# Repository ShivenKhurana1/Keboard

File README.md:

# Keboard

A custom 60% mechanical keyboard featuring an OLED display and rotary encoder for enhanced functionality. coded using [onshape](https://cad.onshape.com/documents/cca7080cfaf346b1d03e6a45/w/840138e854193d740b07961a/e/62251870f6a2fd42355be13b)

## Features

- **60% Layout**: Compact 60-key layout without function row, navigation cluster, or numpad
- **OLED Display**: 0.91" I2C OLED for displaying status, layers, or custom animations
- **Rotary Encoder**: EC11 rotary encoder for volume control, scrolling, or custom functions
- **Hot-Swap Sockets**: Kailh hot-swap sockets for easy switch swapping without soldering
- **RP2040 Controller**: Powered by Raspberry Pi Pico for excellent performance and QMK compatibility

## Gallery

### CAD Design

### Schematics

### PCB Design

## Bill of Materials

|Item                          |Qty  |Link                                                                                                                                                                                                                                                                                                                                                                                                                                                                                                                                                                                                                                                                                                                                                                                                                                                                                                                                    |Price |Running total|
|------------------------------|-----|----------------------------------------------------------------------------------------------------------------------------------------------------------------------------------------------------------------------------------------------------------------------------------------------------------------------------------------------------------------------------------------------------------------------------------------------------------------------------------------------------------------------------------------------------------------------------------------------------------------------------------------------------------------------------------------------------------------------------------------------------------------------------------------------------------------------------------------------------------------------------------------------------------------------------------------|------|-------------|
|Keycaps                       |1 set|[Aliexpress](https://www.aliexpress.us/item/3256809438061445.html?gatewayAdapt=glo2usa4itemAdapt)                                                                                                                                                                                                                                                                                                                                                                                                                                                                                                                                                                                                                                                                                                                                                                                                                                       |13$   |13$          |
|Switches                      |90pc |[Akko V3 Creamy Purple Pro Switch](https://en.akkogear.com/product/akko-v3-creamy-purple-pro-switch/?attribute_quantity=45+pcs&wmc-currency=USD&srsltid=AfmBOoqiLOo9XCgXVcATHmXp4RFQoOtLwqSfavUuphAmf-L9G720cljCm9w)                                                                                                                                                                                                                                                                                                                                                                                                                                                                                                                                                                                                                                                                                                                    |$30.25|43$          |
|OLED                          |1    |[0.91 Inch OLED Display](https://www.aliexpress.us/item/3256808609571956.html?spm=a2g0o.productlist.main.3.48151769KArKuF&algo_pvid=ce0853be-5666-4ee8-8396-2d05b5408b98&algo_exp_id=ce0853be-5666-4ee8-8396-2d05b5408b98-2&pdp_ext_f=%7B%22order%22%3A%2214%22%2C%22eval%22%3A%221%22%2C%22fromPage%22%3A%22search%22%7D&pdp_npi=6%40dis%21USD%215.55%212.49%21%21%2138.01%2117.03%21%402103129017744729562121748e4280%2112000046697912867%21sea%21US%217473440140%21ABX%211%210%21n_tag%3A-29910%3Bd%3A6e694963%3Bm03_new_user%3A-29895%3BpisId%3A5000000200860533&curPageLogUid=osvBYXtlXRIq&utparam-url=scene%3Asearch%7Cquery_from%3A%7Cx_object_id%3A1005008795886708%7C_p_origin_prod%3A)                                                                                                                                                                                                                                        |$5.55 |49$          |
|Raspberry Pi Pico             |1    |[Digikey](https://www.digikey.com/en/products/detail/raspberry-pi/SC0917/16608257)                                                                                                                                                                                                                                                                                                                                                                                                                                                                                                                                                                                                                                                                                                                                                                                                                                                      |$5.00 |54$          |
|EC11 rotary encoder           |1    |[aliexpress](https://www.aliexpress.us/item/3256801690870145.html?spm=a2g0o.productlist.main.13.4a6f4548uMFl9Y&utparam-url=scene%3Asearch%7Cquery_from%3Apc_back_same_best%7Cx_object_id%3A1005001877184897%7C_p_origin_prod%3A&algo_pvid=833f1c90-5076-4091-9ba9-4546061ea109&algo_exp_id=833f1c90-5076-4091-9ba9-4546061ea109&pdp_ext_f=%7B%22order%22%3A%22558%22%2C%22fromPage%22%3A%22search%22%7D&pdp_npi=6%40dis%21USD%210.98%210.90%21%21%210.98%210.90%21%402101eede17744732008168631e148e%2112000017992905728%21sea%21US%217473440140%21ABX%211%210%21n_tag%3A-29910%3Bd%3A6e694963%3Bm03_new_user%3A-29895&gatewayAdapt=4itemAdapt)                                                                                                                                                                                                                                                                                          |$2.60 |56$          |
|PCB                           |1    |JLCPCB                                                                                                                                                                                                                                                                                                                                                                                                                                                                                                                                                                                                                                                                                                                                                                                                                                                                                                                                  |$25.61|82$          |
|Hotswap sockets               |70   |[Aliexpress](https://www.aliexpress.us/item/3256807039037559.html?src=google&pdp_npi=4%40dis%21USD%212.61%211.34%21%21%21%21%21%40%2112000039872158635%21ppc%21%21%21&gatewayAdapt=glo2usa)                                                                                                                                                                                                                                                                                                                                                                                                                                                                                                                                                                                                                                                                                                                                             |$9.54 |92$          |
|Stabilizer Set                |1    |[Aliexpress](https://www.aliexpress.us/item/3256801817127792.html?spm=a2g0o.productlist.main.1.1285SPAgSPAgNv&algo_pvid=c38de26b-7e44-4d31-b39f-cbcb36108078&algo_exp_id=c38de26b-7e44-4d31-b39f-cbcb36108078-0&pdp_ext_f=%7B%22order%22%3A%2232%22%2C%22eval%22%3A%221%22%2C%22fromPage%22%3A%22search%22%7D&pdp_npi=6%40dis%21USD%214.25%214.24%21%21%214.25%214.24%21%402101ef5e17744733813248467e601c%2112000033272651555%21sea%21US%217473440140%21ABX%211%210%21n_tag%3A-29910%3Bd%3A6e694963%3Bm03_new_user%3A-29895%3BpisId%3A5000000200860533&curPageLogUid=1E7nWo6FwrMm&utparam-url=scene%3Asearch%7Cquery_from%3A%7Cx_object_id%3A1005002003442544%7C_p_origin_prod%3A)                                                                                                                                                                                                                                                      |$4.25 |96$          |
|Diodes                        |100  |[aliexpress](https://www.aliexpress.com/ssr/300001493/welcomegiftspmpc?spm=a2g0o.productlist.main.1.39ee0IZO0IZO8Y&businessCode=ug&productIds=1005007160279747&pha_manifest=ssr&source_position=app_home_moretolove_wg&_immersiveMode=true&disableNav=YES&sourceName=SEARCH&skuId=12000039653638113&utparam-url=scene%3Asearch%7Cquery_from%3A%7Cx_object_id%3A1005007160279747%7C_p_origin_prod%3A&pvid=f7c60c86-66dc-4f98-b2b9-71da8c27a6db&_gl=1*1uumsoe*_gcl_aw*R0NMLjE3NzQ0NzI5NjguQ2owS0NRandqNDdPQmhDbUFSSXNBRjV3VUVIMENtcFpqSVQtUmtzZ3BITkVBOGo3dllCaHoyMUZmemRjRmtMSk5ISWxUbGJGTnA1em1SZ2FBajlERUFMd193Y0I.*_gcl_dc*R0NMLjE3NzQzNjE3NzQuQ2owS0NRanc3SWpPQmhEeUFSSXNBRnpyV1F4cWlLQjh3R1NOR2U5Y3dFWDExa2ktb2dHczFJdFFpcjRWcnV6Z1ZwcXlkQVNlS29jeFRuVWFBbzBxRUFMd193Y0I.*_gcl_au*MjEzNDA5NjE3Mi4xNzcyNDE2ODYx*_ga*NzE0ODk3NzI5MjAwMDI0LjE3NzI0MTY4NTcwNzM.*_ga_VED1YSGNC7*czE3NzQ0NzI5NDckbzEzJGcxJHQxNzc0NDczNzIxJGo2MCRsMCRoMA..)|$4.77 |101$         |
|Coupon (3$ off 15$ Aliexpress)|     |                                                                                                                                                                                                                                                                                                                                                                                                                                                                                                                                                                                                                                                                                                                                                                                                                                                                                                                                        |-3    |98$          |

**Total Estimated Cost: ~$100**

### PCB Pricing Example

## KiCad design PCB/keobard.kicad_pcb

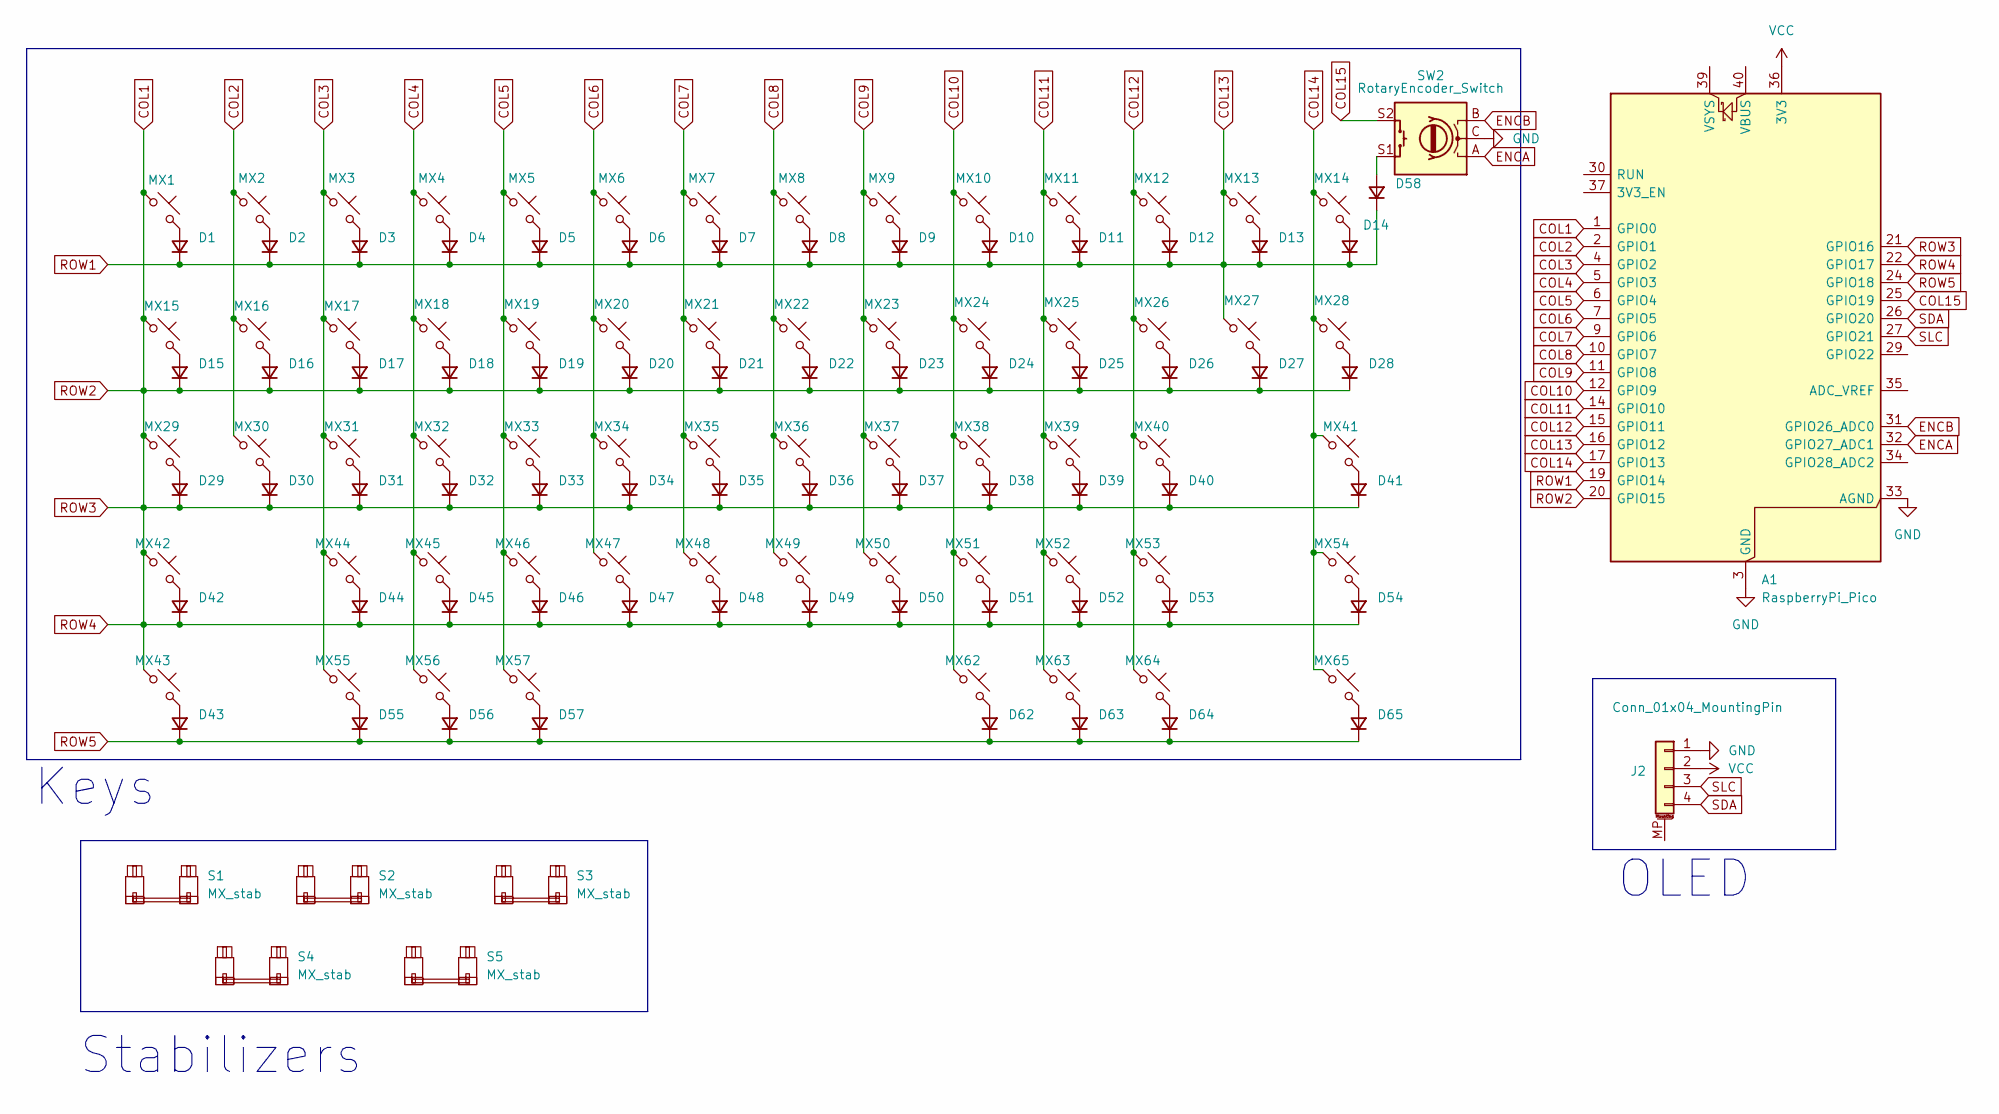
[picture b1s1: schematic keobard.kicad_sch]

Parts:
A1: RaspberryPi_Pico; RaspberryPi_Pico_Common_Unspecified
D1, D2, D3, D4, D5, D6, D7, D8, D9, D10, D11, D12, D13, D14, D15, D16, D17, D18, D19, D20, D21, D22, D23, D24, D25, D26, D27, D28, D29, D30, D31, D32, D33, D34, D35, D36, D37, D38, D39, D40, D41, D42, D43, D44, D45, D46, D47, D48, D49, D50, D51, D52, D53, D54, D55, D56, D57, D58, D62, D63, D64, D65: D_Small; D_SOD-123
J2: Conn_01x04_MountingPin; PinHeader_1x04_P2.54mm_Vertical
MX1, MX2, MX3, MX4, MX5, MX6, MX7, MX8, MX9, MX10, MX11, MX12, MX13, MX14, MX15, MX16, MX17, MX18, MX19, MX20, MX21, MX22, MX23, MX24, MX25, MX26, MX27, MX28, MX29, MX30, MX31, MX32, MX33, MX34, MX35, MX36, MX37, MX38, MX39, MX40, MX41, MX42, MX43, MX44, MX45, MX46, MX47, MX48, MX49, MX50, MX51, MX52, MX53, MX54, MX55, MX56, MX57, MX62, MX63, MX64, MX65: MX_SW_HS; SW_MX_HS_CPG151101S11_1u
S1, S2, S3: MX_stab; STAB_MX_P_2u
S4: MX_stab; STAB_MX_P_2.75u
S5: MX_stab; STAB_MX_P_6.25u
SW2: RotaryEncoder_Switch; RotaryEncoder_Alps_EC11E-Switch_Vertical_H20mm

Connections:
COL1: A1.1 (GPIO0), A1.20 (GPIO15), A1.21 (GPIO16), A1.22 (GPIO17), D15.1 (K), D16.1 (K), D17.1 (K), D18.1 (K), D19.1 (K), D20.1 (K), D21.1 (K), D22.1 (K), D23.1 (K), D24.1 (K), D25.1 (K), D26.1 (K), D27.1 (K), D28.1 (K), D29.1 (K), D30.1 (K), D31.1 (K), D32.1 (K), D33.1 (K), D34.1 (K), D35.1 (K), D36.1 (K), D37.1 (K), D38.1 (K), D39.1 (K), D40.1 (K), D41.1 (K), D42.1 (K), D44.1 (K), D45.1 (K), D46.1 (K), D47.1 (K), D48.1 (K), D49.1 (K), D50.1 (K), D51.1 (K), D52.1 (K), D53.1 (K), D54.1 (K), MX1.1, MX15.1, MX29.1, MX42.1, MX43.1
COL2: A1.2 (GPIO1), MX2.1, MX16.1, MX30.1
COL3: A1.4 (GPIO2), MX3.1, MX17.1, MX31.1, MX44.1, MX55.1
COL4: A1.5 (GPIO3), MX4.1, MX18.1, MX32.1, MX45.1, MX56.1
COL5: A1.6 (GPIO4), MX5.1, MX19.1, MX33.1, MX46.1, MX57.1
COL6: A1.7 (GPIO5), MX6.1, MX20.1, MX34.1, MX47.1
COL7: A1.9 (GPIO6), MX7.1, MX21.1, MX35.1, MX48.1
COL8: A1.10 (GPIO7), MX8.1, MX22.1, MX36.1, MX49.1
COL9: A1.11 (GPIO8), MX9.1, MX23.1, MX37.1, MX50.1
COL10: A1.12 (GPIO9), MX10.1, MX24.1, MX38.1, MX51.1, MX62.1
COL11: A1.14 (GPIO10), MX11.1, MX25.1, MX39.1, MX52.1, MX63.1
COL12: A1.15 (GPIO11), MX12.1, MX26.1, MX40.1, MX53.1, MX64.1
COL13: A1.16 (GPIO12), A1.19 (GPIO14), D1.1 (K), D2.1 (K), D3.1 (K), D4.1 (K), D5.1 (K), D6.1 (K), D7.1 (K), D8.1 (K), D9.1 (K), D10.1 (K), D11.1 (K), D12.1 (K), D13.1 (K), D14.1 (K), D58.1 (K), MX13.1, MX27.1
COL14: A1.17 (GPIO13), MX14.1, MX28.1, MX41.1, MX54.1, MX65.1
COL15: A1.25 (GPIO19), SW2.S2
ENCA: A1.32 (GPIO27_ADC1), SW2.A
ENCB: A1.31 (GPIO26_ADC0), SW2.B
GND: A1.3 (GND), A1.8 (GND), A1.13 (GND), A1.18 (GND), A1.23 (GND), A1.28 (GND), A1.33 (AGND), A1.38 (GND), J2.1, SW2.C
unnamed: D1.2 (A), MX1.2
unnamed: D2.2 (A), MX2.2
unnamed: D3.2 (A), MX3.2
unnamed: D4.2 (A), MX4.2
unnamed: D5.2 (A), MX5.2
unnamed: D6.2 (A), MX6.2
unnamed: D7.2 (A), MX7.2
unnamed: D8.2 (A), MX8.2
unnamed: D9.2 (A), MX9.2
unnamed: D10.2 (A), MX10.2
unnamed: D11.2 (A), MX11.2
unnamed: D12.2 (A), MX12.2
unnamed: D13.2 (A), MX13.2
unnamed: D14.2 (A), MX14.2
unnamed: D15.2 (A), MX15.2
unnamed: D16.2 (A), MX16.2
unnamed: D17.2 (A), MX17.2
unnamed: D18.2 (A), MX18.2
unnamed: D19.2 (A), MX19.2
unnamed: D20.2 (A), MX20.2
unnamed: D21.2 (A), MX21.2
unnamed: D22.2 (A), MX22.2
unnamed: D23.2 (A), MX23.2
unnamed: D24.2 (A), MX24.2
unnamed: D25.2 (A), MX25.2
unnamed: D26.2 (A), MX26.2
unnamed: D27.2 (A), MX27.2
unnamed: D28.2 (A), MX28.2
unnamed: D29.2 (A), MX29.2
unnamed: D30.2 (A), MX30.2
unnamed: D31.2 (A), MX31.2
unnamed: D32.2 (A), MX32.2
unnamed: D33.2 (A), MX33.2
unnamed: D34.2 (A), MX34.2
unnamed: D35.2 (A), MX35.2
unnamed: D36.2 (A), MX36.2
unnamed: D37.2 (A), MX37.2
unnamed: D38.2 (A), MX38.2
unnamed: D39.2 (A), MX39.2
unnamed: D40.2 (A), MX40.2
unnamed: D41.2 (A), MX41.2
unnamed: D42.2 (A), MX42.2
unnamed: D43.2 (A), MX43.2
unnamed: D44.2 (A), MX44.2
unnamed: D45.2 (A), MX45.2
unnamed: D46.2 (A), MX46.2
unnamed: D47.2 (A), MX47.2
unnamed: D48.2 (A), MX48.2
unnamed: D49.2 (A), MX49.2
unnamed: D50.2 (A), MX50.2
unnamed: D51.2 (A), MX51.2
unnamed: D52.2 (A), MX52.2
unnamed: D53.2 (A), MX53.2
unnamed: D54.2 (A), MX54.2
unnamed: D55.2 (A), MX55.2
unnamed: D56.2 (A), MX56.2
unnamed: D57.2 (A), MX57.2
unnamed: D58.2 (A), SW2.S1
unnamed: D62.2 (A), MX62.2
unnamed: D63.2 (A), MX63.2
unnamed: D64.2 (A), MX64.2
unnamed: D65.2 (A), MX65.2
ROW5: A1.24 (GPIO18), D43.1 (K), D55.1 (K), D56.1 (K), D57.1 (K), D62.1 (K), D63.1 (K), D64.1 (K), D65.1 (K)
SDA: A1.26 (GPIO20), J2.4
SLC: A1.27 (GPIO21), J2.3
VCC: A1.36 (3V3), J2.2

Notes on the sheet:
Keys
OLED
Stabilizers

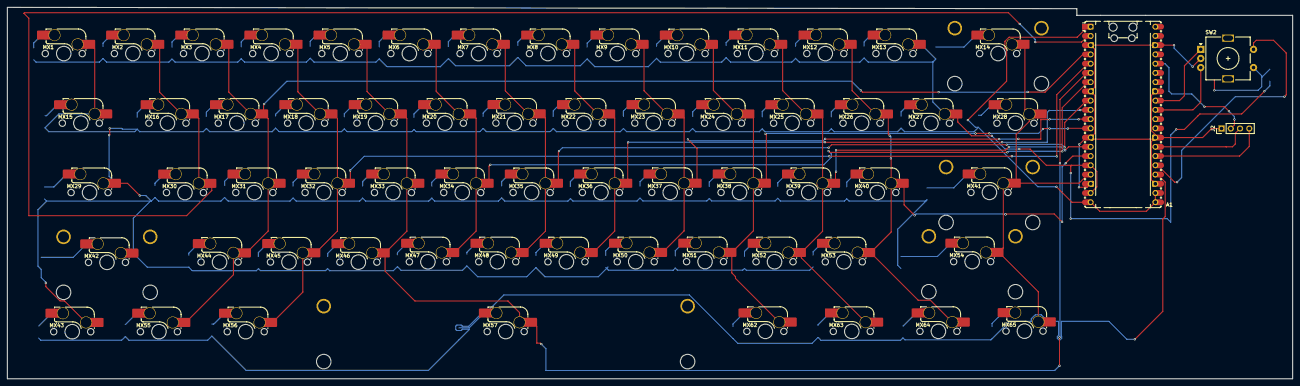
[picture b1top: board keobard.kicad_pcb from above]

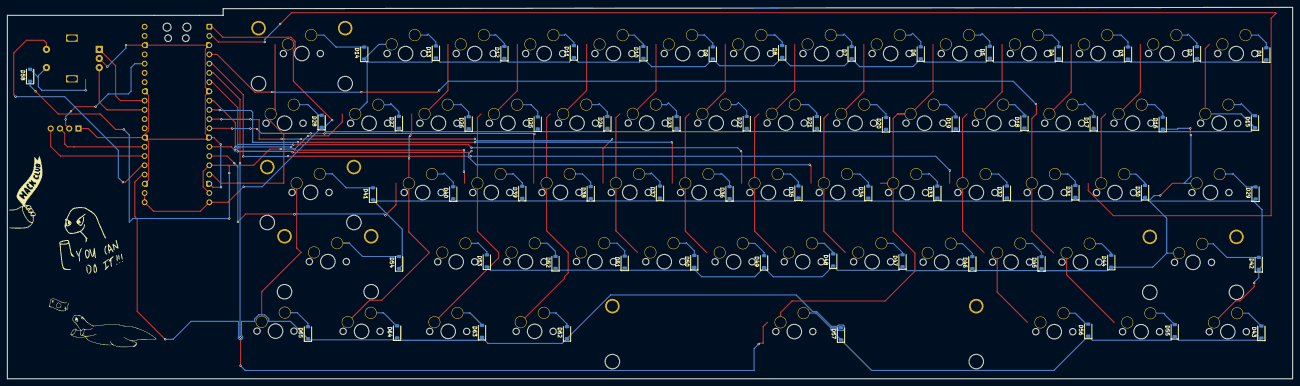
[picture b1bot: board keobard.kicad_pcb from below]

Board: 2 copper layers, 353.3 x 102.1 mm, 133 parts (64 on the bottom side), 84 nets.

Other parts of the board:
"": LOGO
""#2: LOGO

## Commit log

2026-03-24 init
2026-03-24 Add initial README with CAD, Schematics, and PCB images
2026-03-24 Add BOM section to README
    Added a Bill of Materials (BOM) section with item details, quantities, links, prices, and running totals.
2026-03-24 Update headings and add JLCPCB Pricing section
2026-03-24 Add schematics section with image
2026-03-24 knobb
2026-03-24 Add keyboard features and tools to README
    Added a description of the keyboard features and tools used.
2026-03-25 Revise README for Keboard project details
    Updated the README to provide a detailed overview of the Keboard project, including features, gallery, and bill of materials.
2026-03-25 Remove USB-C Connectivity from README
    Removed USB-C connectivity feature from the README.
2026-03-25 Revise parts list with updated prices and sources
    Updated component prices and links in the parts list.
2026-03-25 Revise keyboard description with Onshape reference
    Updated project description to include Onshape link.
2026-03-25 Update README.md with latest project details
    Removed outdated information and merged updates from upstream.
2026-03-25 Refactor Bill of Materials table and update costs
    Updated the Bill of Materials table format and adjusted prices.
